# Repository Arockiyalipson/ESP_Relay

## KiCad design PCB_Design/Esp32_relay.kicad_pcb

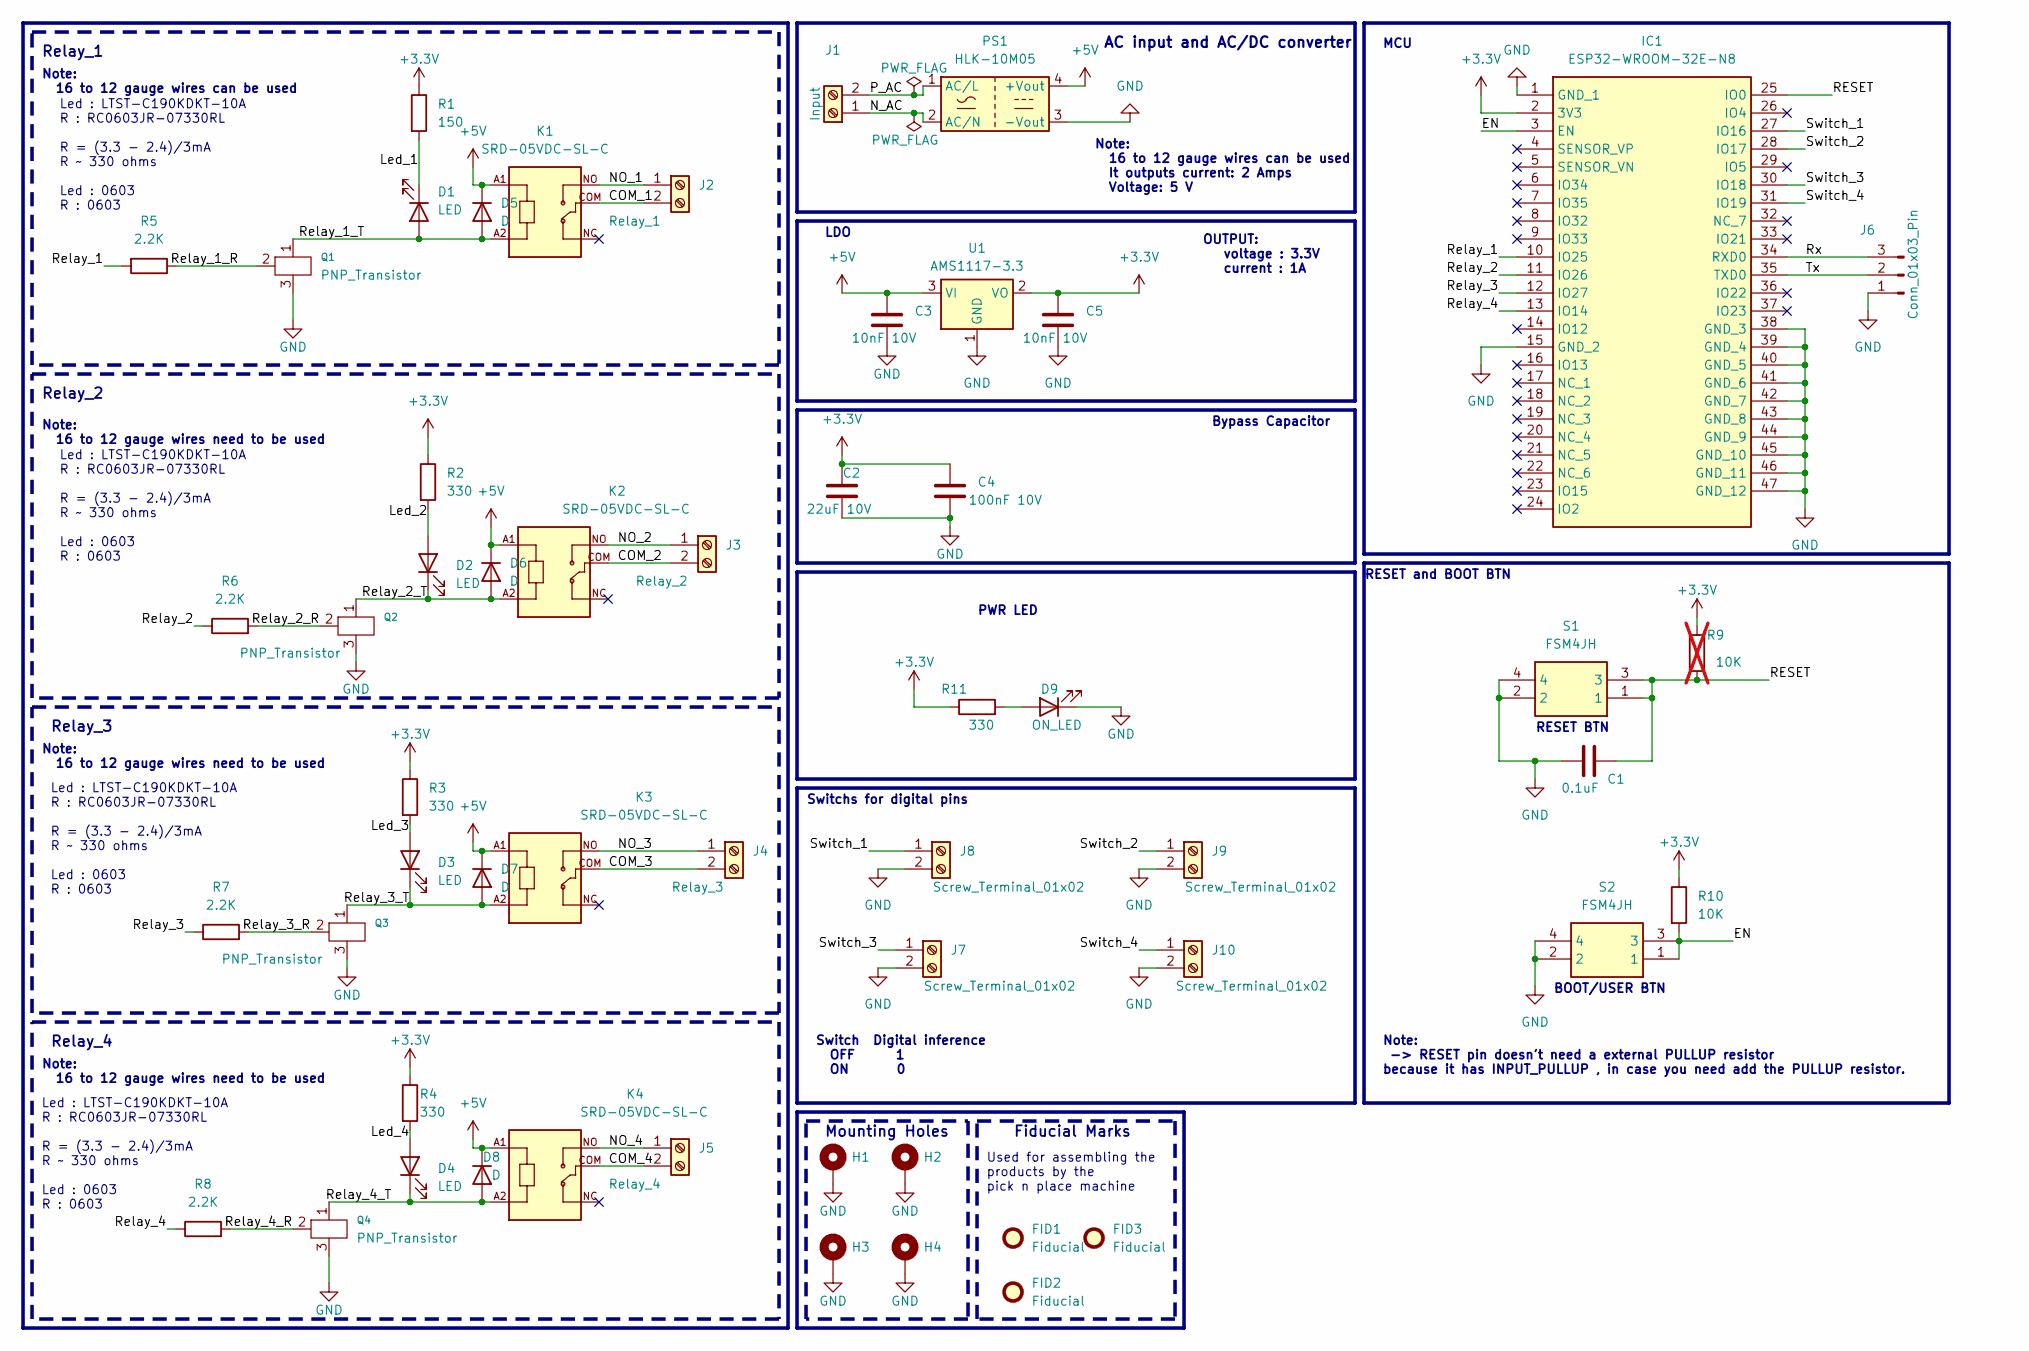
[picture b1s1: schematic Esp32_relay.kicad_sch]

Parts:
C1: 0.1uF; C_0805_2012Metric; Manufacturer_Part_Number C0805C104J8RACTU
C2: 22uF 10V; C_0805_2012Metric; Manufacturer_Part_Number CL21A226MPQNNNE
C3, C5: 10nF 10V; C_0805_2012Metric; Manufacturer_Part_Number 885012007009
C4: 100nF 10V; C_0805_2012Metric; Manufacturer_Part_Number C0805C104J5RAC
D1, D2, D3, D4: LED; LED_1206_3216Metric; Manufacturer_Part_Number 156120VS75000
D5, D6, D7, D8: D; D_0805_2012Metric; Manufacturer_Part_Number BZY55C9V1 RBG
D9: ON_LED; LED_1206_3216Metric; Manufacturer_Part_Number 156120VS75000
FID1, FID2, FID3: Fiducial; Fiducial_1.5mm_Mask3mm
H1, H2, H3, H4: MountingHole_Pad; MountingHole_2.5mm_Pad; Manufacturer_Part_Number ----
IC1: ESP32-WROOM-32E-N8; ESP32WROOM32EN8; Mouser Part Number 356-ESP32WRM32E164PH
J1: Input; TerminalBlock_MetzConnect_Type175_RT02702HBLC_1x02_P7.50mm_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
J2: Relay_1; TerminalBlock_MetzConnect_Type175_RT02702HBLC_1x02_P7.50mm_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
J3: Relay_2; TerminalBlock_MetzConnect_Type175_RT02702HBLC_1x02_P7.50mm_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
J4: Relay_3; TerminalBlock_MetzConnect_Type175_RT02702HBLC_1x02_P7.50mm_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
J5: Relay_4; TerminalBlock_MetzConnect_Type175_RT02702HBLC_1x02_P7.50mm_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
J6: Conn_01x03_Pin; PinHeader_1x03_P2.54mm_Vertical; Manufacturer_Part_Number ----
J7, J8, J9, J10: Screw_Terminal_01x02; TerminalBlock_MetzConnect_Type175_RT02702HBLC_1x02_P7.50mm_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
K1, K2, K3, K4: SRD-05VDC-SL-C; RELAY_SRD-05VDC-SL-C; Manufacturer_Part_Number SRD-05VDC-SL-C
PS1: HLK-10M05; Converter_ACDC_HiLink_HLK-10Mxx; Manufacturer_Part_Number RW-317
Q1, Q2, Q3, Q4: PNP_Transistor; SOT-23; Manufacturer_Part_Number 5203
R1: 150; R_0805_2012Metric; Manufacturer_Part_Number CRCW0805150RFKEAC
R2, R3, R4, R11: 330; R_0805_2012Metric; Manufacturer_Part_Number CRCW0805150RFKEAC
R5, R6, R7, R8: 2.2K; R_0805_2012Metric; Manufacturer_Part_Number CRCW08052K20FKEA
R9: 10K; R_0805_2012Metric; Manufacturer_Part_Number CR0805-FX-1002ELF; not fitted
R10: 10K; R_0805_2012Metric; Manufacturer_Part_Number CR0805-FX-1002ELF
S1, S2: FSM4JH; Mouser Part Number 506-FSM4JH
U1: AMS1117-3.3; SOT-223-3_TabPin2; Manufacturer_Part_Number AMS1117-3.3

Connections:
+3.3V: C2.1, C4.1, C5.1, IC1.2 (3V3), R1.1, R2.1, R3.1, R4.1, R9.1, R10.1, R11.1, U1.2 (VO)
+5V: C3.1, D5.1 (K), D6.1 (K), D7.1 (K), D8.1 (K), K1.A1, K2.A1, K3.A1, K4.A1, PS1.4 (+Vout), U1.3 (VI)
/COM_1: J2.2, K1.COM
/COM_2: J3.2, K2.COM
/COM_3: J4.2, K3.COM
/COM_4: J5.2, K4.COM
/EN: IC1.3 (EN), R10.2, S2.1, S2.3
/Led_1: D1.1 (K), R1.2
/Led_2: D2.2 (A), R2.2
/Led_3: D3.2 (A), R3.2
/Led_4: D4.2 (A), R4.2
/NO_1: J2.1, K1.NO
/NO_2: J3.1, K2.NO
/NO_3: J4.1, K3.NO
/NO_4: J5.1, K4.NO
/N_AC: J1.1, PS1.2 (AC/N)
/P_AC: J1.2, PS1.1 (AC/L)
/RESET: C1.2, IC1.25 (IO0), R9.2, S1.1, S1.3
/Relay_1: IC1.10 (IO25), R5.2
/Relay_1_R: Q1.2, R5.1
/Relay_1_T: D1.2 (A), D5.2 (A), K1.A2, Q1.1
/Relay_2: IC1.11 (IO26), R6.1
/Relay_2_R: Q2.2, R6.2
/Relay_2_T: D2.1 (K), D6.2 (A), K2.A2, Q2.1
/Relay_3: IC1.12 (IO27), R7.1
/Relay_3_R: Q3.2, R7.2
/Relay_3_T: D3.1 (K), D7.2 (A), K3.A2, Q3.1
/Relay_4: IC1.13 (IO14), R8.1
/Relay_4_R: Q4.2, R8.2
/Relay_4_T: D4.1 (K), D8.2 (A), K4.A2, Q4.1
/Rx: IC1.34 (RXD0), J6.3
/Switch_1: IC1.27 (IO16), J8.1
/Switch_2: IC1.28 (IO17), J9.1
/Switch_3: IC1.30 (IO18), J7.1
/Switch_4: IC1.31 (IO19), J10.1
/Tx: IC1.35 (TXD0), J6.2
GND: C1.1, C2.2, C3.2, C4.2, C5.2, D9.1 (K), H1.1, H2.1, H3.1, H4.1, IC1.1 (GND_1), IC1.15 (GND_2), IC1.38 (GND_3), IC1.39 (GND_4), IC1.40 (GND_5), IC1.41 (GND_6), IC1.42 (GND_7), IC1.43 (GND_8), IC1.44 (GND_9), IC1.45 (GND_10), IC1.46 (GND_11), IC1.47 (GND_12), J6.1, J7.2, J8.2, J9.2, J10.2, PS1.3 (-Vout), Q1.3, Q2.3, Q3.3, Q4.3, S1.2, S1.4, S2.2, S2.4, U1.1 (GND)
unnamed: D9.2 (A), R11.2

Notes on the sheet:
Note: -> RESET pin doesn't need a external PULLUP resistor because it has INPUT_PULLUP , in case you need add the PULLUP resistor.
Relay_4
Led : LTST-C190KDKT-10A R : RC0603JR-07330RL R = (3.3 - 2.4)/3mA R ~ 330 ohms Led : 0603 R : 0603
Relay_3
Relay_1
Used for assembling the products by the pick n place machine
AC input and AC/DC converter
OUTPUT: voltage : 3.3V current : 1A
PWR LED
Fiducial Marks
Relay_2
Switch Digital inference OFF 1 ON 0
Note: 16 to 12 gauge wires need to be used
RESET BTN
RESET and BOOT BTN
Switchs for digital pins
Note: 16 to 12 gauge wires can be used It outputs current: 2 Amps Voltage: 5 V
Note: 16 to 12 gauge wires can be used
Mounting Holes
Bypass Capacitor
MCU
LDO
BOOT/USER BTN

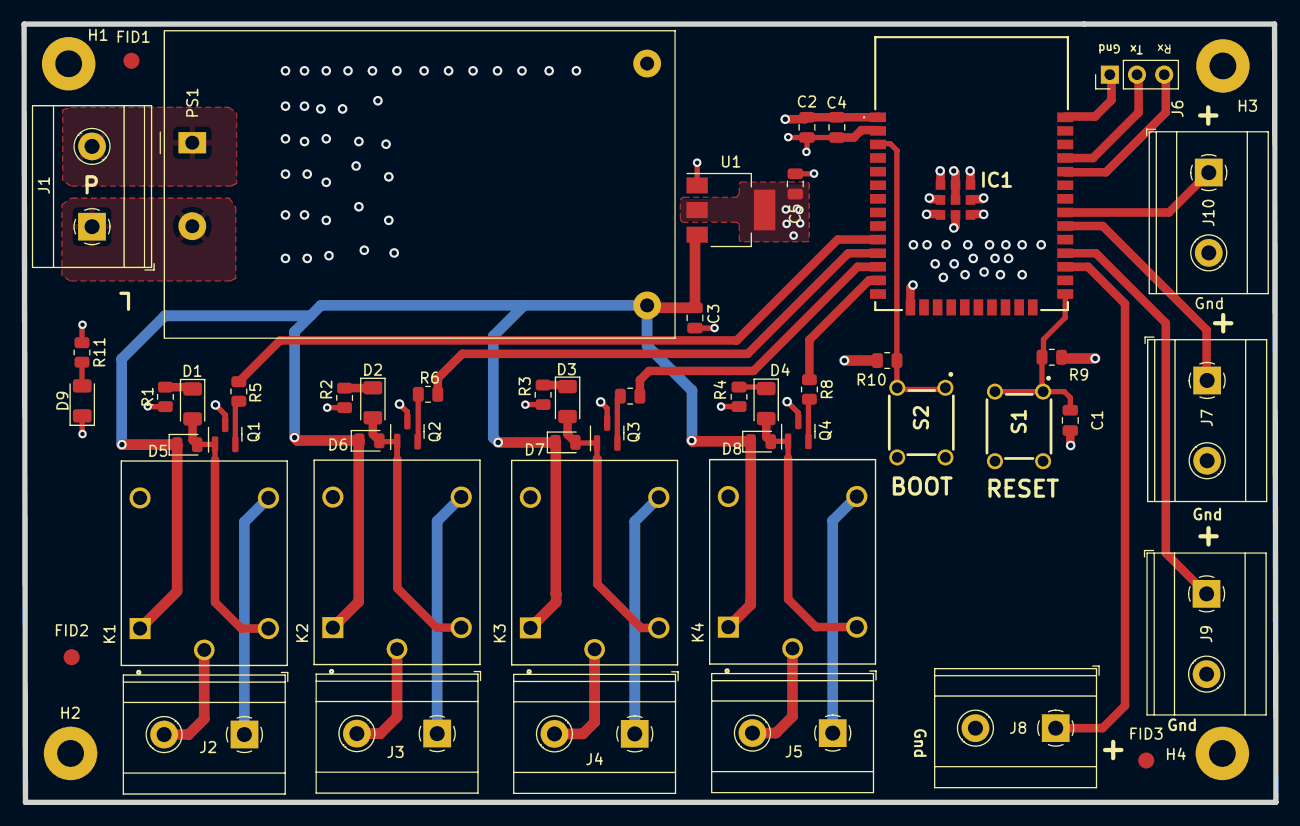
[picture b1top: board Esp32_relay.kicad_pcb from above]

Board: 4 copper layers, 117.0 x 72.7 mm, 55 parts (0 on the bottom side), 38 nets.
